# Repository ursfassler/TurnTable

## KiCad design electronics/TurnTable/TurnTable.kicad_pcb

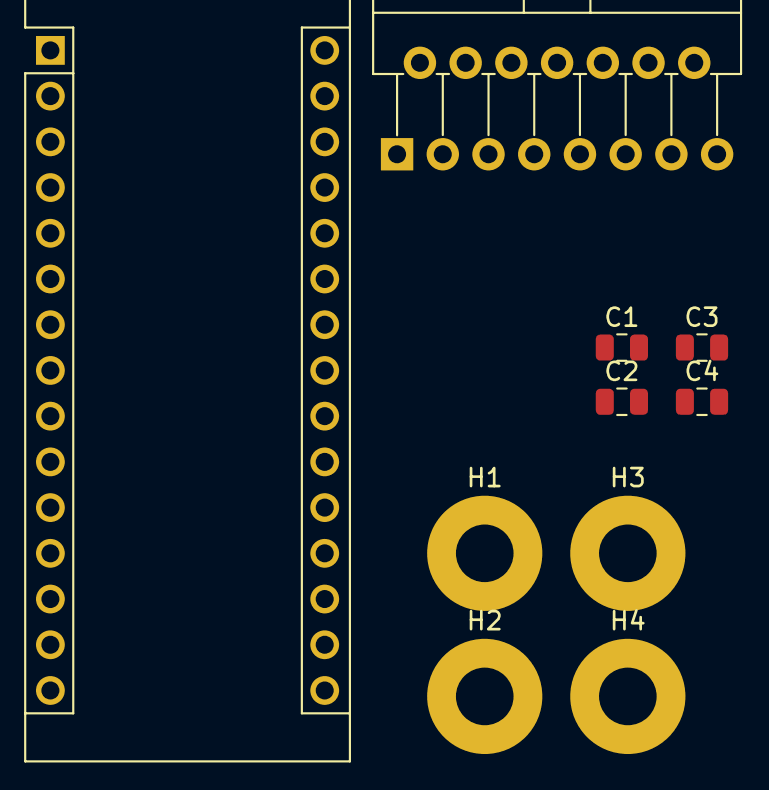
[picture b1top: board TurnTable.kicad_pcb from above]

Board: 2 copper layers, 10 parts (0 on the bottom side), 8 nets, no tracks yet.

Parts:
A1: Arduino_Nano_v3.x; Arduino_Nano
C1, C2: 100n; C_0805_2012Metric
C3, C4: 10u; C_0805_2012Metric
H1, H2, H3, H4: MountingHole; MountingHole_3.2mm_M3_Pad
U1: L298HN; TO-220-15_P2.54x2.54mm_StaggerOdd_Lead4.58mm_Vertical

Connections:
+5V: A1.30, C1.1, C2.1, C3.1, C4.1, U1.4, U1.9
/EnA: A1.12, U1.6
/EnB: A1.15, U1.11
/IN1: A1.10, U1.5
/IN2: A1.11, U1.7
/IN3: A1.13, U1.10
/IN4: A1.14, U1.12
GND: A1.4, A1.29, C1.2, C2.2, C3.2, C4.2, U1.1, U1.8, U1.15

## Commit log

2021-09-25 add a gear library
2021-09-25 simple model of the servo
2021-09-25 optimize usability
2021-09-25 set pressure_angle to 'standard value'
2021-09-25 further work
2021-09-26 add gears library from my own fork
2021-09-28 add more gears
2021-09-28 optimize small gears
2021-09-28 update assembly
2021-10-02 fit worm gear to servo
2021-10-02 add holes to the great gear
2021-10-03 add guidings
2021-10-16 integrate servo holder
2021-10-16 correct height of servo holder
2021-10-16 add worm gear holder
2021-12-14 add a second motor
2021-12-14 reduce number of fragments to prevent slicing error
2022-03-12 inital firmware commit
2022-03-12 add Drive module
2022-03-13 don't make warnings to errors
2022-03-13 move Stopped to first position in enum
2022-03-13 add switching delay to prevent short circuit
2022-03-13 create RemoteControl module
2022-03-13 optimize the printed output
2022-03-14 test ble characteristic event handler
2022-03-14 use enum class for State of Drive
2022-03-17 move tests to own folder
2023-12-16 switch to wifi board and blinking light
2023-12-16 add a feature
2023-12-16 add cucumber feature and run it
2023-12-16 add cucumber workflow
2023-12-16 cd into folder and execute there
2023-12-24 add settings and extensions recommendations
2023-12-24 more configuration
2023-12-24 correct indentation
2023-12-24 correct indentation again
2023-12-24 simple mqtt example
2023-12-24 add persistency feature
2023-12-25 replace old unit-tests with embedded test framework
2023-12-25 enable native environment
2023-12-26 rename environments and set default environment
2023-12-26 automatically added files.associations
2023-12-26 some formatting for readability
2023-12-26 persisting wifi ssid
2023-12-26 add automatically generated files.associations
2023-12-26 use correct data type to prevent warning
2023-12-27 some cleanup
2023-12-27 add ms-vscode.cmake-tools as recommended extension
2023-12-27 flash target directly from container
2023-12-28 add test step for persistency
2023-12-28 go back to working cucumber version
2023-12-28 upgrade to latest cucumber-cpp
2023-12-28 only enable used cucumber-cpp features
    Also install and use cucumber and gtest from system directories.
